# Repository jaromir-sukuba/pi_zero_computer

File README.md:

# Raspberry pi portable computer #

## What it is ##
This is small handheld computer, built around Raspberry Pi Zero, referred as RPi in following articles. Though RPi is often thought to be complete computer, it isn't. You need to add some kind of display, input devices (mouse, keyboard or similar), power supply and perhaps network connection to make it usable by today standards.

My decision was to pack it into small portable form. Raspberry pi laptops have been done to death online, but all of them do miss some features I like to have:

1. All-in-one form factor. I don't want one box for brains, another box for BT keyboard, another for USB hub etc... It is simpler from construction point of view, but the device isn't much usable nor portable.
2. Enclosure sturdy enough so I can put the computer into by backpack with no worries of its disintegration. 
3. At least two USB ports, audio output, battery life at least 5 hours.
4. No major modifications to Raspberry pi. 
5. Easy to replicate by others. I mean - off the shelf components, no complicated wiring (once the PCB is done).

I must admit this computer goes in line with my long term "portable computer fixation", exhibited [before](https://hackaday.io/project/18445-brainfcktor), [and here](https://hackaday.io/project/3511-pavapro-portable-avr-programmer), [also here](https://hackaday.io/project/1757-pp04-camel-computer) or [here too](https://hackaday.io/project/643-minibsd-laptop-computer).

## What it isn't ##
This device isn't superior to thousands or millions manhours of cummulative work put even into the cheapest smartphone you can buy at usual sources. Despite all the work invested into the devices, those are fit to majority of users and (from obvious reasons) often miss details vital for folks like me - full sized USB ports or GPIO pins attached to main processor or 3,5mm audio jack.

## FAQ ##
Q: How is this better than my phone/tablet/smart toaster?

A: If you need to ask this question, then it isn't any better.

## Hardware ##
All hardware is monted on two PCBs, sandwitched together.

The smaller one contains TFT display and a few minor components, vast majority of components is on bottom PCB.

The circuit seems to be complex, but in fact it's only a bit convoluted power supply and user interface. 

RPi acts as heart of this, with USB hub based on FE1.1s, attached to WiFi module, STM32F072 enumerating as USB HID device with two interfaces - one for keyboard (operated by 4x4 matrix keyboard) and one for mouse (operated by analog joystick and three discrete buttons). Audio comes as no surprise to Raspberry pi users, it done by low-pass RC filter and jelly-bean TDA1308 in most common circuit. STM32L011 is connected to RPi by means of serial interface and can turn on/off three power supply voltages (for RPi, for USB, for WiFi) on request of RPi or user. Power is taken from two LiPo cells in series, those are charged by MCP73844 from external 10V source.

Enclosure is designed in FreeCad and printed on hobbyist grade DIY 3D printer

Though self tapered screws would do the job too, I used threaded inserts for machined screws, to allow multiple open-close cycles.

Software
I tried to use as little custom software as possible and rely on existing software drivers. That is behind decision of placing the keyboard behind USB HID wall or using RTL8188EUS module for WiFi. Despite that, device doesn't work as-is with mainstream Raspbian distribution, some customized setup is needed.

* download raspbian, create bootable uSD card and put file ssh.txt into /boot of the uSD card - to allow ssh access to RPi
* connect USB-Ethernet convertor into one USB port of device. 3USD one from Asian sources will do the job
* start device, wait a bit, discover it's IP, login, run raspi-config, setup new password, expand filesystem
* run sudo apt-get update
* run sudo apt-get upgrade
* Add to file /etc/modules-load.d/fbtft.conf
> 	spi-bcm2835
> 	fbtft_device

* Add to file /etc/modprobe.d/fbtft.conf
> 	options fbtft_device custom name=fb_ili9341 gpios=reset:25,dc:24,led:18 speed=16000000 rotate=90 bgr=1

* sudo nano /boot/config.txt
> 	dtoverlay=rpi-display

* sudo reboot
*	sudo nano /boot/cmdline.txt
	
> 	fbcon=map:10 fbcon=font:VGA7x14 logo.nologo

*	sudo nano /usr/share/X11/xorg.conf.d/99-fbdev.conf
> 		Section "Device"
> 		  Identifier "bla"
> 		  Driver "fbdev"
> 		  Option "fbdev" "/dev/fb1"
> 		EndSection
 		
 now you should be able to see display working

* in /boot/config.txt add the following line to enable audio interface:
>     dtoverlay=pwm-2chan,pin=18,func=2,pin2=13,func2=4
>     audio_pwm_mode=2
	
* sudo reboot
* sudo apt-get purge rfkill - to prevent WiFi module from sleeping

## Arduino, just for blog cred ##
Yes, you can upload your arduino sketches in the field

## Miscellany ##
More info is to be found on my [hackady.io page](https://hackaday.io/project/19437-raspberry-pi-zero-handheld-computer)

This project is licensed by MIT license, see LICENSE.md file

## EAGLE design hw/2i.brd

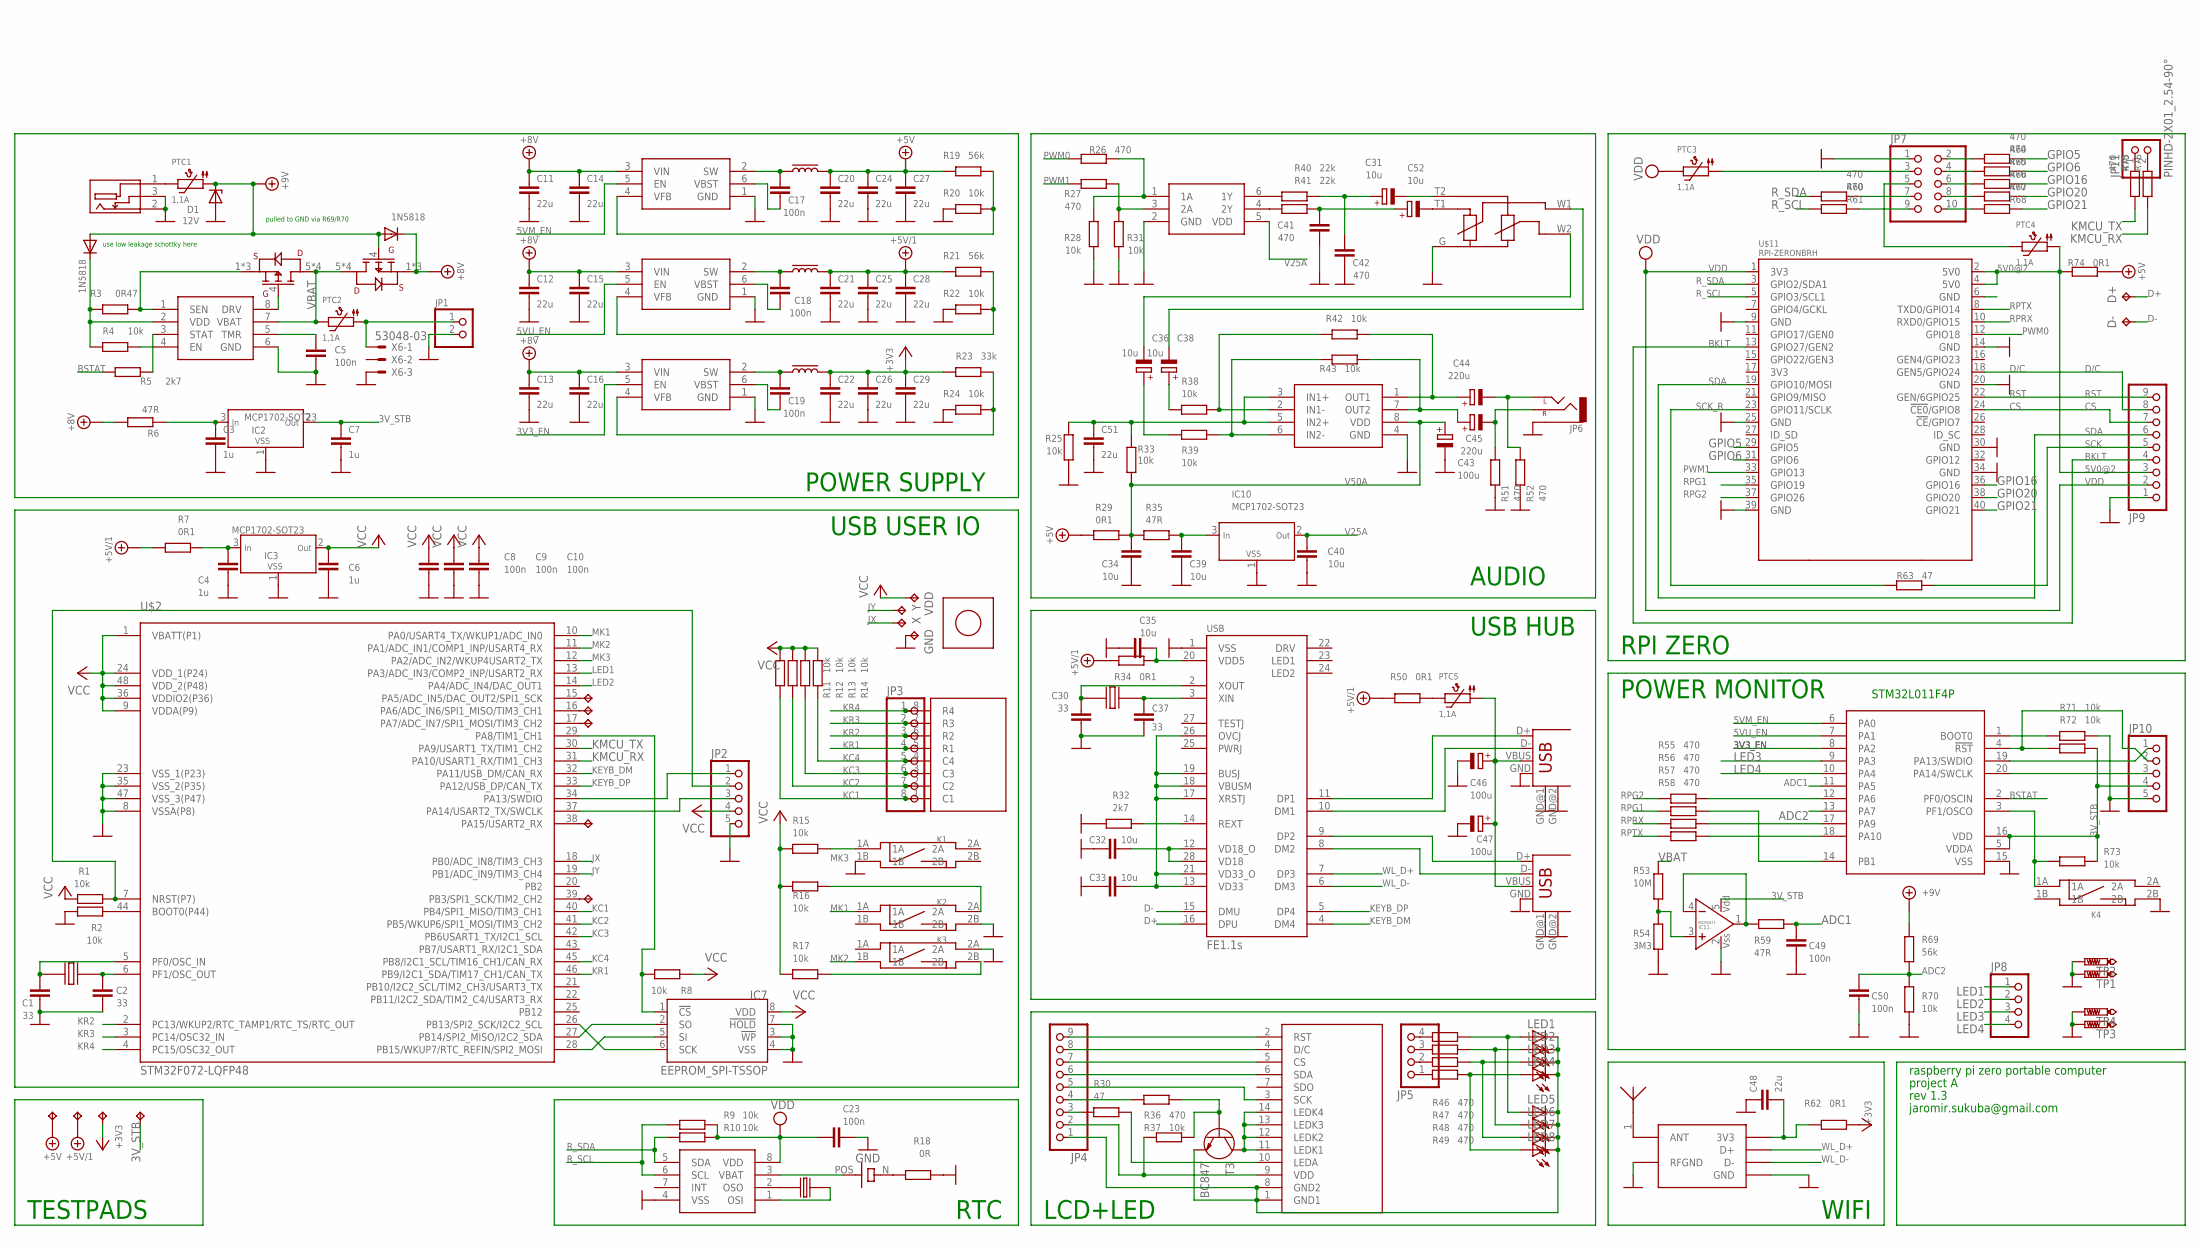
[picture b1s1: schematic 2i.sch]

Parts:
ANT1: ANT_RAINSUN_24GHZ; ANT_RAINSUN-24G
C1, C2, C30, C37: 33; R0805
C3, C4, C6, C7: 1u; R0805
C5, C8, C9, C10, C17, C18, C19, C23, C49, C50: 100n; R0805
C11, C12, C13, C14, C15, C16, C20, C21, C22, C24, C25, C26, C27, C28, C29, C48, C51: 22u; R0805
C31, C36, C38, C52: 10u; PANASONIC_A
C32, C33, C34, C35, C39, C40: 10u; R0805
C41, C42: 470; R0805
C43, C46, C47: 100u; PANASONIC_D
C44, C45: 220u; PANASONIC_D
D1: 12V; SMB
D2, D3: 1N5818; SMB
D+: TPTP14R; TP14R
D-: TPTP14R; TP14R
GND: TPTP14R; TP14R
IC1: MCP73844; MSOP8
IC2, IC3, IC10: MCP1702-SOT23; SOT23
IC4, IC5, IC6: TPS562200; SOT23-6
IC7: EEPROM_SPI-TSSOP; TSSOP8W
IC8: PCF8523; SO-08
IC9: 74LVC2G34; SOT23-6
IC11: MCP6021; SOT23-5L
JP1: PINHD-1X02_2.54-90°; 1X02/90
JP2, JP10: PINHD-1X05_2.54-90°; 1X05/90
JP3: PINHD-1X08_2.54; 1X08
JP4, JP9: PINHD-1X09_2.00; 1X09M
JP5, JP8: PINHD-1X04_2.00; 1X04M
JP6: AUDIO-JACKPTH; AUDIO-JACK
JP7: PINHD-2X05_2.54-90°; 2X05/90
JP11: PINHD-2X01_2.54-90°; 2X01/90
K1, K2, K3, K4: SWITCH_BD_B; SW_SMD2
LED1, LED2, LED3, LED4: LED3MM
LED5, LED6, LED7, LED8: LEDCHIPLED_0805; CHIPLED_0805
MOD1: MOD_USB_RTL8188
PTC1, PTC2, PTC3, PTC4, PTC5: 1,1A; PTC1812
Q1: CRYSTAL87X38; CRYST_32K_87X38MM
R1, R2, R4, R8, R9, R10, R11, R12, R13, R14, R15, R16, R17, R20, R22, R24, R25, R28, R31, R33, R37, R38, R39, R42, R43, R70, R71, R72, R73: 10k; R0805
R3: 0R47; R1206
R5, R32: 2k7; R0805
R6, R35, R59: 47R; R0805
R7, R29, R34, R50, R62, R74: 0R1; R1206
R18: 0R; R0805
R19, R21, R69: 56k; R0805
R23: 33k; R0805
R26, R27, R36, R46, R47, R48, R49, R51, R52, R55, R56, R57, R58, R60, R61, R64, R65, R66, R67, R68, R75, R76: 470; R0805
R30, R63: 47; R0805
R40, R41: 22k; R0805
R53: 10M; R0805
R54: 3M3; R0805
T1, T2: PFET_SO8; SO-08
T3: BC847; SOT23
TFT1: DISP_ILI_28
TP1, TP2, TP3, TP4: PTR1PAD1-13; P1-13
U$1: CONN_DC_13; CON_DC13
U$2: STM32F072-LQFP48; LQFP48
U$3, U$4, U$5: 2u2; BOURNS_SRP7030
U$6: BATTH1220; BATT_HOLDER_DS1092-12
U$7: KB1604
U$8: JOY_PS
U$9: TDA1308; SO-08
U$10: POT_DUAL_14X2; POT_14X2DUAL
U$11: RPI-ZERONBRH; RPI_ZERO_NBRH
U$12: STM32F030_20; TSSOP20
USB: FE1.1S; FE1.1S_SSOP-28
USB1, USB2: USB-A-S
VDD: TPTP14R; TP14R
X, X1, X3, X4, X5, X7, X8, X9, X12, X13: TPTP14R; TP14R
X2, X14: CRYST_TC26SMXAS; CR_12SMXA_S
X6: 53048-03
Y: TPTP14R; TP14R

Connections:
3V3_EN: IC6.5 (EN), U$12.8 (PA2)
3V_STB: C7.1, IC2.2 (OUT), IC11.5 (VDD), JP10.4, R72.2, R73.2, U$12.5 (VDDA), U$12.16 (VDD), X5.TP
5V0@2: JP9.3, PTC4.P$1 (1), R74.2, U$11.2 (5V0), U$11.4 (5V0)
5VM_EN: IC4.5 (EN), U$12.6 (PA0)
5VU_EN: IC5.5 (EN), U$12.7 (PA1)
+3V3: C22.1, C26.1, C29.1, R23.1, R62.1, U$5.P$2, X4.TP
+5V: C20.1, C24.1, C27.1, R19.1, R29.2, R74.1, U$3.P$2, X1.TP
+5V/1: C21.1, C25.1, C28.1, R7.1, R21.1, R34.2, R50.2, U$4.P$2, X3.TP
+8V: C11.1, C12.1, C13.1, C14.1, C15.1, C16.1, D3.C, IC4.3 (VIN), IC5.3 (VIN), IC6.3 (VIN), R6.2, T2.1 (S), T2.2 (S), T2.3 (S)
+9V: D1.C, D2.A, D3.A, PTC1.P$1 (1), R69.2, T2.4 (G)
ADC1: C49.2, R59.1, U$12.11 (PA5)
ADC2: C50.2, R69.1, R70.2, U$12.13 (PA7)
BKLT: JP9.4, U$11.13 (GPIO27/GEN2)
BSTAT: R5.2, U$12.2 (PF0/OSCIN)
CS: JP9.7, U$11.24 (!CE0!/GPIO8)
D+: D+.TP, USB.16 (DPU)
D-: D-.TP, USB.15 (DMU)
D/C: JP9.8, U$11.18 (GEN5/GPIO24)
GND: C1.1, C2.1, C3.2, C4.2, C5.2, C6.2, C7.2, C8.2, C9.2, C10.2, C11.2, C12.2, C13.2, C14.2, C15.2, C16.2, C20.2, C21.2, C22.2, C23.2, C24.2, C25.2, C26.2, C27.2, C28.2, C29.2, C30.1, C32.1, C33.1, C34.1, C35.1, C37.1, C39.1, C40.1, C41.1, C42.1, C43.-, C46.-, C47.-, C48.1, C49.1, C50.1, C51.2, D1.A, GND.TP, IC1.6 (GND), IC2.1 (VSS), IC3.1 (VSS), IC4.1 (GND), IC5.1 (GND), IC6.1 (GND), IC7.3 (!WP), IC7.4 (VSS), IC7.7 (!HOLD), IC8.4 (VSS), IC9.2 (GND), IC10.1 (VSS), IC11.2 (VSS), JP1.2, JP2.5, JP6.SLEEVE, JP7.1, JP9.1, JP10.5, K1.1B, K2.2B, K3.2A, K4.2B, MOD1.GND, MOD1.RFGND, R2.2, R18.1, R20.1, R22.1, R24.1, R25.1, R28.1, R31.1, R32.1, R51.2, R52.2, R54.1, R70.1, R71.2, TP1.TP, TP2.TP, TP3.TP, TP4.TP, U$1.2 (N), U$1.3 (SW), U$2.8 (VSSA(P8)), U$2.23 (VSS_1(P23)), U$2.35 (VSS_2(P35)), U$2.47 (VSS_3(P47)), U$9.4 (GND), U$10.G, U$11.9 (GND), U$11.14 (GND), U$11.20 (GND), U$11.25 (GND), U$11.30 (GND), U$11.34 (GND), U$11.39 (GND), U$12.15 (VSS), USB.1 (VSS), USB1.GND, USB1.GND@1 (GND), USB1.GND@2 (GND), USB2.GND, USB2.GND@1 (GND), USB2.GND@2 (GND), X6.3
GND@8: U$11.6 (GND)
GPIO5: R64.2, U$11.29 (GPIO5)
GPIO6: R65.2, U$11.31 (GPIO6)
GPIO16: R66.2, U$11.36 (GPIO16)
GPIO20: R67.2, U$11.38 (GPIO20)
GPIO21: R68.2, U$11.40 (GPIO21)
JX: U$2.18 (PB0/ADC_IN8/TIM3_CH3), X.TP
JY: U$2.19 (PB1/ADC_IN9/TIM3_CH4), Y.TP
KC1: JP3.8, R11.1, U$2.40 (PB4/SPI1_MISO/TIM3_CH1), U$7.1 (C1)
KC2: JP3.7, R12.1, U$2.41 (PB5/WKUP6/SPI1_MOSI/TIM3_CH2), U$7.2 (C2)
KC3: JP3.6, R13.1, U$2.42 (PB6USART1_TX/I2C1_SCL), U$7.3 (C3)
KC4: JP3.5, R14.1, U$2.45 (PB8/I2C1_SCL/TIM16_CH1/CAN_RX), U$7.4 (C4)
KEYB_DM: U$2.32 (PA11/USB_DM/CAN_RX), USB.4 (DM4)
KEYB_DP: U$2.33 (PA12/USB_DP/CAN_TX), USB.5 (DP4)
KMCU_RX: R76.1, U$2.31 (PA10/USART1_RX/TIM1_CH3)
KMCU_TX: R75.1, U$2.30 (PA9/USART1_TX/TIM1_CH2)
KR1: JP3.4, U$2.46 (PB9/I2C1_SDA/TIM17_CH1/CAN_TX), U$7.5 (R1)
KR2: JP3.3, U$2.2 (PC13/WKUP2/RTC_TAMP1/RTC_TS/RTC_OUT), U$7.6 (R2)
KR3: JP3.2, U$2.3 (PC14/OSC32_IN), U$7.7 (R3)
KR4: JP3.1, U$2.4 (PC15/OSC32_OUT), U$7.8 (R4)
LED1: JP8.1, U$2.13 (PA3/ADC_IN3/COMP2_INP/USART2_RX)
LED2: JP8.2, U$2.14 (PA4/ADC_IN4/DAC_OUT1)
LED3: JP8.3, U$12.9 (PA3)
LED4: JP8.4, U$12.10 (PA4)
MK1: K2.1A, U$2.10 (PA0/USART4_TX/WKUP1/ADC_IN0)
MK2: K3.1B, U$2.11 (PA1/ADC_IN1/COMP1_INP/USART4_RX)
MK3: K1.1A, R15.2, U$2.12 (PA2/ADC_IN2/WKUP4USART2_TX)
unnamed: C35.2, R34.1, USB.20 (VDD5)
unnamed: C17.2, IC4.2 (SW), U$3.P$1
unnamed: JP4.3, R30.2
unnamed: IC7.6 (SCK), U$2.26 (PB13/SPI2_SCK/I2C2_SCL)
unnamed: R36.2, R37.1, T3.1 (B)
unnamed: JP4.4, R36.1
unnamed: IC1.1 (SEN), R3.2, T1.1 (S), T1.2 (S), T1.3 (S)
unnamed: USB.9 (DP2), USB2.D+
unnamed: USB.8 (DM2), USB2.D-
unnamed: USB.10 (DM1), USB1.D-
unnamed: IC1.8 (DRV), T1.4 (G)
unnamed: IC1.4 (EN), R4.2
unnamed: USB.11 (DP1), USB1.D+
unnamed: C33.2, USB.13 (VD33), USB.17 (XRSTJ), USB.18 (VBUSM), USB.19 (BUSJ), USB.21 (VD33_O), USB.26 (OVCJ)
unnamed: IC11.1 (VYSTUP), IC11.4 (IN-), R59.2
unnamed: C32.2, USB.12 (VD18_O), USB.28 (VD18)
unnamed: C5.1, IC1.5 (TMR)
unnamed: C17.1, IC4.6 (VBST)
unnamed: R32.2, USB.14 (REXT)
unnamed: IC4.4 (VFB), R19.2, R20.2
unnamed: C30.2, USB.2 (XOUT), X14.P$1
unnamed: C18.2, IC5.2 (SW), U$4.P$1
unnamed: C18.1, IC5.6 (VBST)
unnamed: C37.2, USB.3 (XIN), X14.P$2
unnamed: C46.+, C47.+, PTC5.P$1 (1), USB1.VBUS, USB2.VBUS
unnamed: IC7.2 (SO), U$2.27 (PB14/SPI2_MISO/I2C2_SDA)
unnamed: IC9.6 (1Y), R40.2
unnamed: IC9.4 (2Y), R41.2
unnamed: C31.+, C42.2, R40.1
unnamed: C41.2, C52.+, R41.1
unnamed: C44.-, JP6.TIP (LEFT), R52.1
unnamed: C45.-, JP6.RING (RIGHT), R51.1
unnamed: C44.+, R42.2, U$9.1 (OUT1)
unnamed: C45.+, R43.2, U$9.7 (OUT2)
unnamed: C51.1, R25.2, R33.1, U$9.3 (IN1+), U$9.5 (IN2+)
unnamed: R38.2, R42.1, U$9.2 (IN1-)
unnamed: R39.2, R43.1, U$9.6 (IN2-)
unnamed: C38.+, R38.1
unnamed: C36.+, R39.1
unnamed: C36.-, U$10.W2
unnamed: C38.-, U$10.W1
unnamed: ANT1.1, MOD1.ANT
unnamed: JP11.1, R75.2
unnamed: IC5.4 (VFB), R21.2, R22.2
unnamed: C19.2, IC6.2 (SW), U$5.P$1
unnamed: C19.1, IC6.6 (VBST)
unnamed: JP2.1, U$2.34 (PA13/SWDIO)
unnamed: IC6.4 (VFB), R23.2, R24.2
unnamed: C4.1, IC3.3 (IN), R7.2
unnamed: JP2.3, U$2.37 (PA14/USART2_TX/SWCLK)
unnamed: D2.C, IC1.2 (VDD), R3.1, R4.1
unnamed: PTC1.P$2 (2), U$1.1
unnamed: IC9.1 (1A), R26.1, R28.2
unnamed: IC9.3 (2A), R27.1, R31.2
unnamed: C1.2, U$2.5 (PF0/OSC_IN), X2.P$1
unnamed: JP11.2, R76.2
unnamed: IC7.5 (SI), U$2.28 (PB15/WKUP7/RTC_REFIN/SPI2_MOSI)
unnamed: IC7.1 (!CS), R8.2, U$2.29 (PA8/TIM1_CH1)
unnamed: R56.2, U$12.14 (PB1)
unnamed: U$2.15 (PA5/ADC_IN5/DAC_OUT2/SPI1_SCK), X7.TP
unnamed: R2.1, U$2.44 (BOOT0(P44))
unnamed: JP5.4, R46.2
unnamed: JP5.3, R47.2
unnamed: JP5.2, R48.2
unnamed: JP5.1, R49.2
unnamed: JP2.2, R1.1, U$2.7 (NRST(P7))
unnamed: R57.2, U$12.17 (PA9)
unnamed: R58.2, U$12.18 (PA10)
unnamed: PTC5.P$2 (2), R50.1
unnamed: R55.2, U$12.12 (PA6)
unnamed: U$2.16 (PA6/ADC_IN6/SPI1_MISO/TIM3_CH1), X8.TP
unnamed: U$2.17 (PA7/ADC_IN7/SPI1_MOSI/TIM3_CH2), X9.TP
unnamed: U$2.38 (PA15/USART2_RX), X12.TP
unnamed: U$2.39 (PB3/SPI1_SCK/TIM2_CH2), X13.TP
unnamed: JP10.1, U$12.19 (PA13/SWDIO)
unnamed: JP10.3, U$12.20 (PA14/SWCLK)
unnamed: JP10.2, R72.1, U$12.4 (!RST)
unnamed: JP1.1, PTC2.P$1 (1), X6.1
unnamed: C52.-, U$10.T1
unnamed: K4.1A, R73.1, U$12.3 (PF1/OSCO)
unnamed: C2.2, U$2.6 (PF1/OSC_OUT), X2.P$2
unnamed: IC8.3 (VBAT), U$6.POS
unnamed: R18.2, U$6.N (M)
unnamed: LED1.A, LED5.A, R46.1
unnamed: LED2.A, LED6.A, R47.1
unnamed: K3.2B, R17.2
unnamed: IC8.2 (OSO), Q1.4 (2)
unnamed: IC8.1 (OSI), Q1.1
unnamed: K2.2A, R16.2
unnamed: LED3.A, LED7.A, R48.1
unnamed: LED4.A, LED8.A, R49.1
unnamed: JP4.5, TFT1.3 (SCK)
unnamed: JP4.1, LED1.K (C), LED2.K (C), LED3.K (C), LED4.K (C), LED5.C, LED6.C, LED7.C, LED8.C, T3.2 (E), TFT1.1 (GND1), TFT1.8 (GND2)
unnamed: T3.3 (C), TFT1.11 (LEDK1), TFT1.12 (LEDK2), TFT1.13 (LEDK3), TFT1.14 (LEDK4)
unnamed: JP7.5, PTC4.P$2 (2)
unnamed: IC1.3 (STAT), R5.1
unnamed: JP7.3, PTC3.P$1 (1)
unnamed: C48.2, MOD1.3V3, R62.2
unnamed: IC11.3 (NEIN+), R53.1, R54.2
unnamed: C3.1, IC2.3 (IN), R6.1
unnamed: R71.1, U$12.1 (BOOT0)
unnamed: C31.-, U$10.T2
unnamed: R30.1, TFT1.10 (LEDA)
unnamed: JP4.2, R37.2, TFT1.9 (VDD)
unnamed: C39.2, IC10.3 (IN), R35.2
unnamed: JP4.6, TFT1.6 (SDA)
unnamed: JP4.7, TFT1.5 (CS)
unnamed: JP4.8, TFT1.4 (D/C)
unnamed: JP4.9, TFT1.2 (RST)
unnamed: JP7.10, R68.1
unnamed: JP7.8, R67.1
unnamed: JP7.6, R66.1
unnamed: JP7.4, R65.1
unnamed: JP7.2, R64.1
unnamed: JP7.7, R60.2
unnamed: JP7.9, R61.2
PWM0: R27.2, U$11.12 (GPIO18)
PWM1: R26.2, U$11.33 (GPIO13)
RPG1: R56.1, U$11.35 (GPIO19)
RPG2: R55.1, U$11.37 (GPIO26)
RPRX: R57.1, U$11.10 (RXD0/GPIO15)
RPTX: R58.1, U$11.8 (TXD0/GPIO14)
RST: JP9.9, U$11.22 (GEN/6GPIO25)
R_SCL: IC8.6 (SCL), R9.1, R61.1, U$11.5 (GPIO3/SCL1)
R_SDA: IC8.5 (SDA), R10.1, R60.1, U$11.3 (GPIO2/SDA1)
SCK: JP9.5, R63.1
SCK_R: R63.2, U$11.23 (GPIO11/SCLK)
SDA: JP9.6, U$11.19 (GPIO10/MOSI)
V25A: C40.2, IC9.5 (VDD), IC10.2 (OUT)
V50A: C34.2, C43.+, R29.1, R33.2, R35.1, U$9.8 (VDD)
VBAT: IC1.7 (VBAT), PTC2.P$2 (2), R53.2, T1.5 (D), T1.6 (D), T1.7 (D), T1.8 (D), T2.5 (D), T2.6 (D), T2.7 (D), T2.8 (D)
VCC: C6.1, C8.1, C9.1, C10.1, IC3.2 (OUT), IC7.8 (VDD), JP2.4, R1.2, R8.1, R11.2, R12.2, R13.2, R14.2, R15.1, R16.1, R17.1, U$2.1 (VBATT(P1)), U$2.9 (VDDA(P9)), U$2.24 (VDD_1(P24)), U$2.36 (VDDIO2(P36)), U$2.48 (VDD_2(P48)), VDD.TP
VDD: C23.1, IC8.8 (VDD), JP9.2, PTC3.P$2 (2), R9.2, R10.2, U$11.1 (3V3)
WL_D+: MOD1.D+, USB.7 (DP3)
WL_D-: MOD1.D-, USB.6 (DM3)

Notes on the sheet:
POWER SUPPLY
USB USER IO
RPI ZERO
POWER MONITOR
WIFI
LCD+LED
USB HUB
AUDIO
raspberry pi zero portable computer
project A
rev 1.3
RTC
jaromir.sukuba@gmail.com
pulled to GND via R69/R70
use low leakage schottky here
TESTPADS
STM32L011F4P

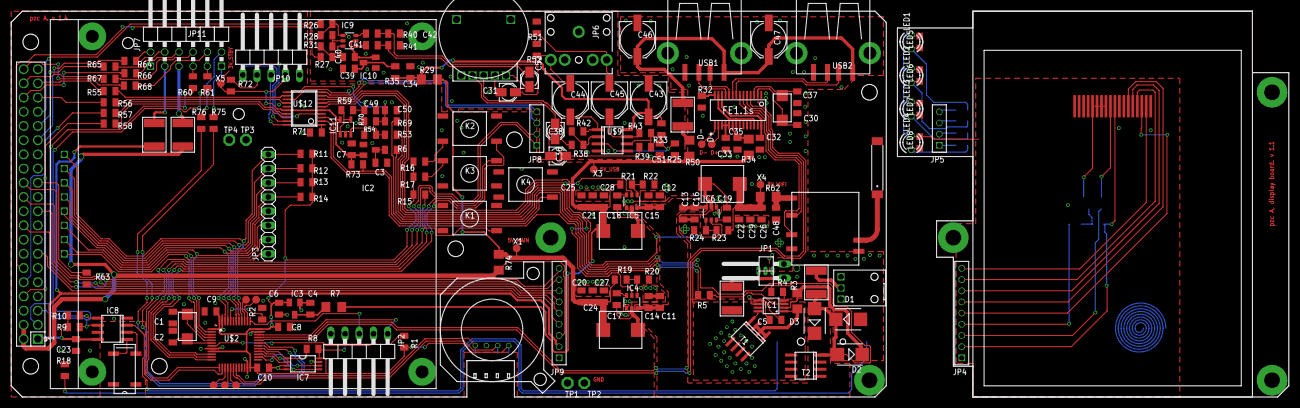
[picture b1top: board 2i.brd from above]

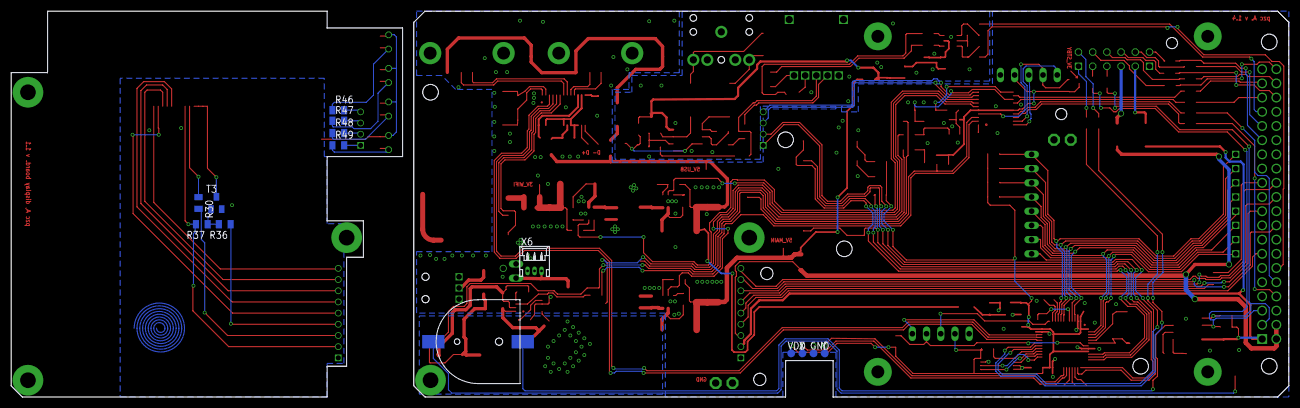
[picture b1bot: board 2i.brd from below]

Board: 2 copper layers, 228.5 x 69.0 mm, 212 parts (14 on the bottom side), 180 nets.

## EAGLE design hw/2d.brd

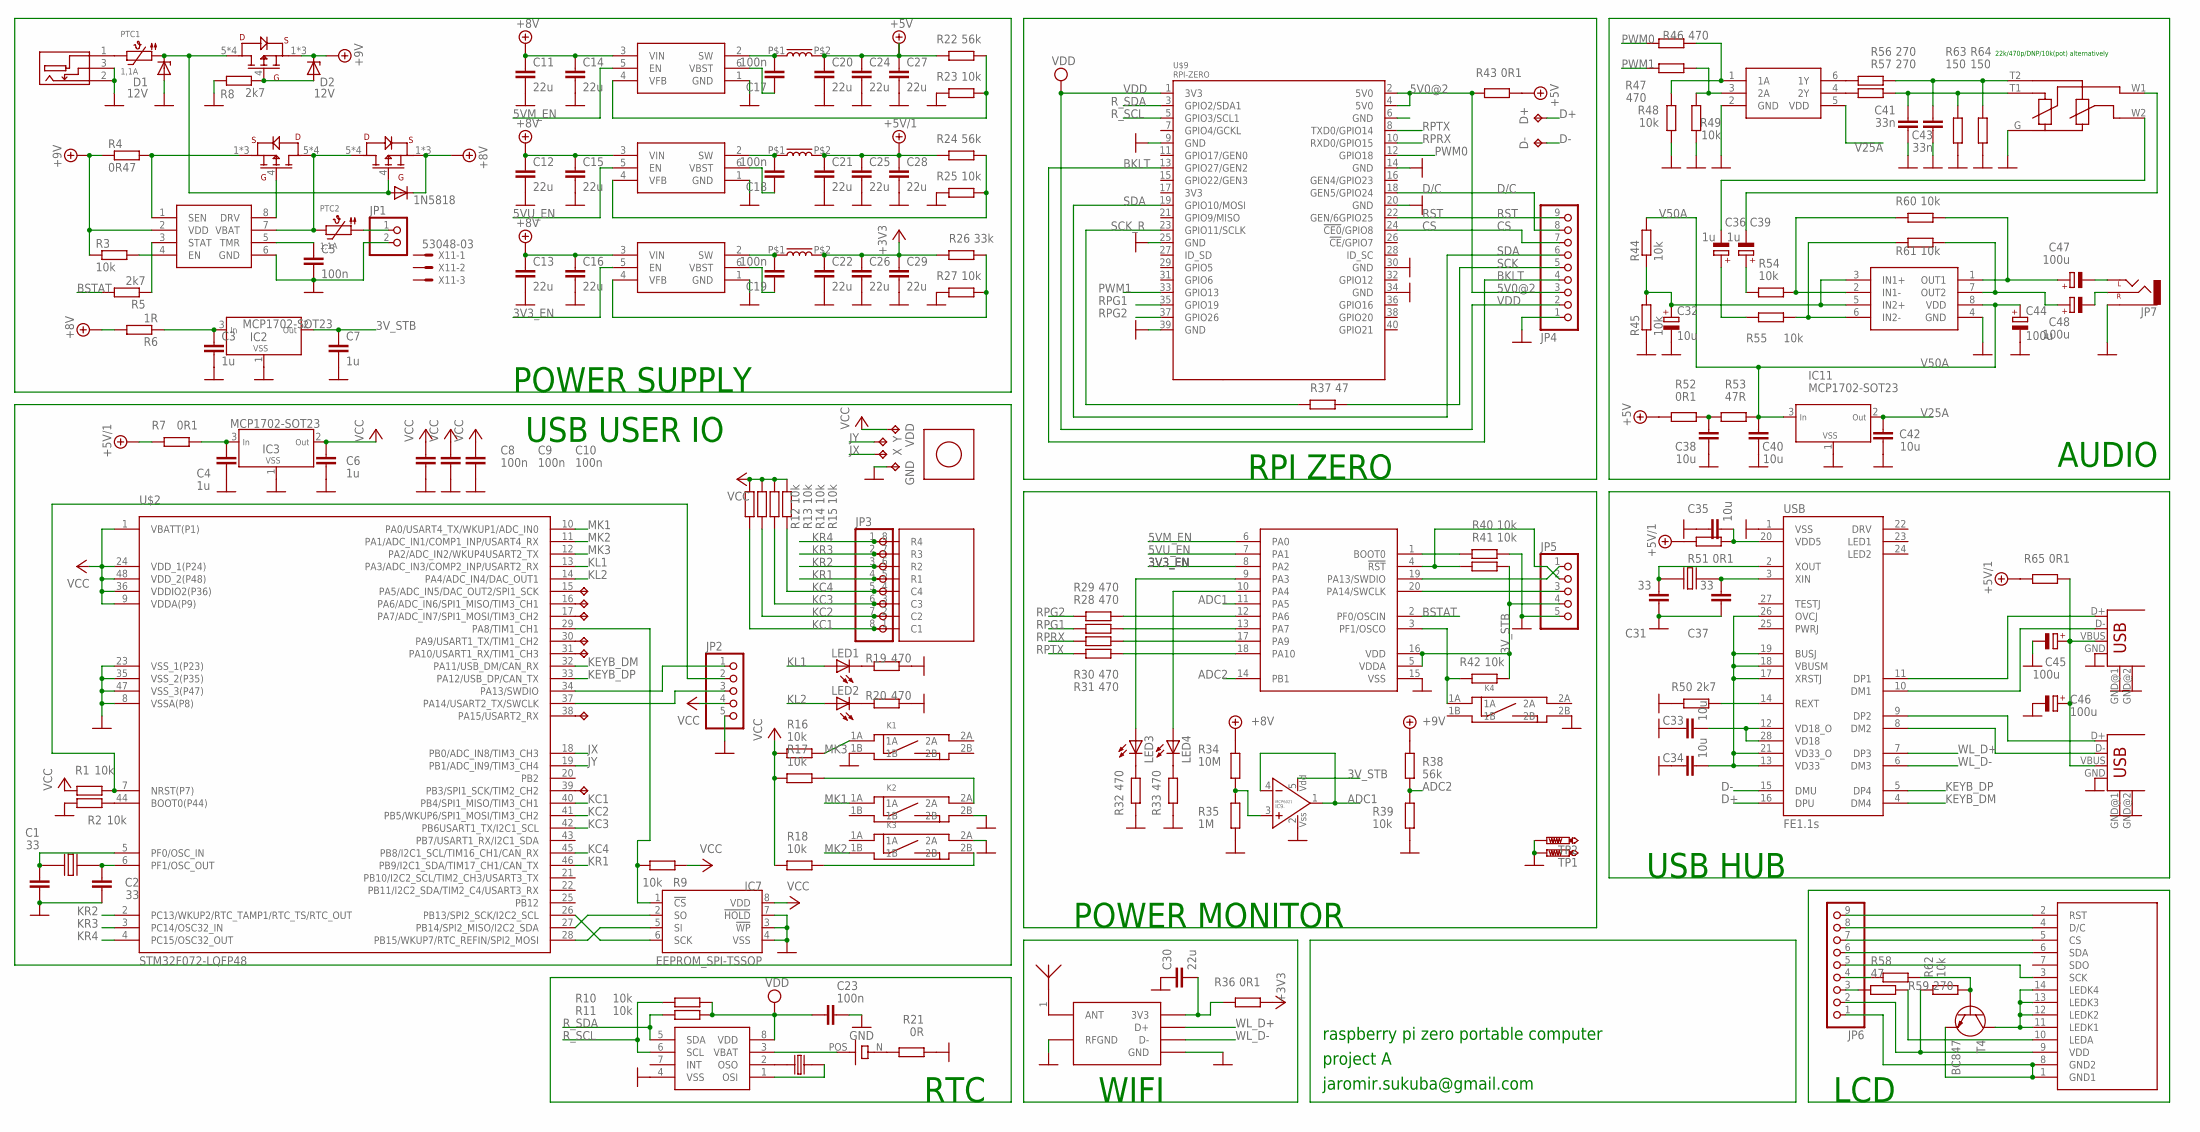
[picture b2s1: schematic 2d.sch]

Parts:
ANT1: ANT_RAINSUN_24GHZ; ANT_RAINSUN-24G
C1, C2, C31, C37: 33; R0805
C3, C4, C6, C7: 1u; R0805
C5, C8, C9, C10, C17, C18, C19, C23: 100n; R0805
C11, C12, C13, C14, C15, C16, C20, C21, C22, C24, C25, C26, C27, C28, C29, C30: 22u; R0805
C32: 10u; PANASONIC_B
C33, C34, C35, C38, C40, C42: 10u; R0805
C36, C39: 1u; PANASONIC_A
C41, C43: 33n; R0805
C44, C45, C46, C47, C48: 100u; PANASONIC_D
D1: 12V; SMB
D2: 12V; SOD80C
D3: 1N5818; SMB
D+: TPTP14R; TP14R
D-: TPTP14R; TP14R
GND: TPTP14R; TP14R
IC1: MCP73844; MSOP8
IC2, IC3, IC11: MCP1702-SOT23; SOT23
IC4, IC5, IC6: TPS562200; SOT23-6
IC7: EEPROM_SPI-TSSOP; TSSOP8W
IC8: PCF8523; SO-08
IC9: MCP6021; SOT23-5L
IC10: 74LVC2G34; SOT23-6
JP1: PINHD-1X02_2.54-90°; 1X02/90
JP2, JP5: PINHD-1X05_2.54-90°; 1X05/90
JP3: PINHD-1X08_2.54; 1X08
JP4, JP6: PINHD-1X09_2.00; 1X09M
JP7: AUDIO-JACKPTH; AUDIO-JACK
K1, K2, K3, K4: SWITCH_BD_B; SW_SMD2
LED1, LED2, LED3, LED4: LED3MM
MOD1: MOD_USB_RTL8188
PTC1, PTC2: 1,1A; PTC1812
Q1: CRYSTAL87X38; CRYST_32K_87X38MM
R1, R2, R3, R9, R10, R11, R12, R13, R14, R15, R16, R17, R18, R23, R25, R27, R39, R40, R41, R42, R44, R45, R48, R49, R54, R55, R60, R61, R62: 10k; R0805
R4: 0R47; R1206
R5, R8, R50: 2k7; R0805
R6: 1R; R0805
R7, R36, R43, R51, R52, R65: 0R1; R1206
R19, R20, R28, R29, R30, R31, R32, R33, R46, R47: 470; R0805
R21: 0R; R0805
R22, R24, R38: 56k; R0805
R26: 33k; R0805
R34: 10M; R0805
R35: 1M; R0805
R37, R58: 47; R0805
R53: 47R; R0805
R56, R57, R59: 270; R0805
R63, R64: 150; R0805
T1, T2, T3: PFET_SO8; SO-08
T4: BC847; SOT23
TFT1: DISP_ILI_28
TP1, TP2: PTR1PAD1-13; P1-13
U$1: CONN_DC_13; CON_DC13
U$2: STM32F072-LQFP48; LQFP48
U$3, U$4, U$5: 2u2; BOURNS_SRP7030
U$6: BATTH1220; BATT_HOLDER_DS1092-12
U$7: KB1604
U$8: JOY_PS
U$9: RPI-ZERO; RASPBERRYPI_BASTELSTUBE_V13_RASPI_BOARD_B+_FULL
U$10: STM32F030_20; TSSOP20
U$11: TDA1308; SO-08
U$12: POT_DUAL_14X2; POT_14X2DUAL
USB: FE1.1S; FE1.1S_SSOP-28
USB1, USB2: USB-A-S
VDD: TPTP14R; TP14R
X, X2, X3, X4, X5, X6, X7, X8: TPTP14R; TP14R
X1, X9: CRYST_TC26SMXAS; CR_12SMXA_S
X11: 53048-03
Y: TPTP14R; TP14R

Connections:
3V3_EN: IC6.5 (EN), U$10.8 (PA2)
3V_STB: C7.1, IC2.2 (OUT), IC9.5 (VDD), JP5.4, R41.2, R42.2, U$10.5 (VDDA), U$10.16 (VDD)
5V0@2: JP4.3, R43.2, U$9.2 (5V0), U$9.4 (5V0)
5VM_EN: IC4.5 (EN), U$10.6 (PA0)
5VU_EN: IC5.5 (EN), U$10.7 (PA1)
+3V3: C22.1, C26.1, C29.1, R26.1, R36.1, U$5.P$2
+5V: C20.1, C24.1, C27.1, R22.1, R43.1, R52.2, U$3.P$2
+5V/1: C21.1, C25.1, C28.1, R7.1, R24.1, R51.2, R65.2, U$4.P$2
+8V: C11.1, C12.1, C13.1, C14.1, C15.1, C16.1, D3.C, IC4.3 (VIN), IC5.3 (VIN), IC6.3 (VIN), R6.2, R34.2, T3.1 (S), T3.2 (S), T3.3 (S)
+12V: D2.C, IC1.2 (VDD), R3.1, R4.1, R38.2, T1.1 (S), T1.2 (S), T1.3 (S)
ADC1: IC9.1 (VYSTUP), IC9.4 (IN-), U$10.11 (PA5)
ADC2: R38.1, R39.2, U$10.14 (PB1)
BKLT: JP4.4, U$9.13 (GPIO27/GEN2)
BSTAT: R5.2, U$10.2 (PF0/OSCIN)
CS: JP4.7, U$9.24 (!CE0!/GPIO8)
D+: D+.TP, USB.16 (DPU)
D-: D-.TP, USB.15 (DMU)
D/C: JP4.8, U$9.18 (GEN5/GPIO24)
GND: C1.1, C2.1, C3.2, C4.2, C5.2, C6.2, C7.2, C8.2, C9.2, C10.2, C11.2, C12.2, C13.2, C14.2, C15.2, C16.2, C20.2, C21.2, C22.2, C23.2, C24.2, C25.2, C26.2, C27.2, C28.2, C29.2, C30.1, C31.1, C32.-, C33.1, C34.1, C35.1, C37.1, C38.1, C40.1, C41.1, C42.1, C43.1, C44.-, C45.-, C46.-, D1.A, GND.TP, IC1.6 (GND), IC2.1 (VSS), IC3.1 (VSS), IC4.1 (GND), IC5.1 (GND), IC6.1 (GND), IC7.3 (!WP), IC7.4 (VSS), IC7.7 (!HOLD), IC8.4 (VSS), IC9.2 (VSS), IC10.2 (GND), IC11.1 (VSS), JP1.2, JP2.5, JP4.1, JP5.5, JP7.SLEEVE, K1.1B, K2.2B, K3.2A, K4.2B, MOD1.GND, MOD1.RFGND, R2.2, R8.1, R19.1, R20.1, R21.1, R23.1, R25.1, R27.1, R32.1, R33.1, R35.1, R39.1, R40.2, R45.1, R48.1, R49.1, R50.1, R63.2, R64.2, TP1.TP, TP2.TP, U$1.2 (N), U$1.3 (SW), U$2.8 (VSSA(P8)), U$2.23 (VSS_1(P23)), U$2.35 (VSS_2(P35)), U$2.47 (VSS_3(P47)), U$9.9 (GND), U$9.14 (GND), U$9.20 (GND), U$9.25 (GND), U$9.30 (GND), U$9.34 (GND), U$9.39 (GND), U$10.15 (VSS), U$11.4 (GND), U$12.G, USB.1 (VSS), USB1.GND, USB1.GND@1 (GND), USB1.GND@2 (GND), USB2.GND, USB2.GND@1 (GND), USB2.GND@2 (GND)
GND@8: U$9.6 (GND)
JX: U$2.18 (PB0/ADC_IN8/TIM3_CH3), X.TP
JY: U$2.19 (PB1/ADC_IN9/TIM3_CH4), Y.TP
KC1: JP3.8, R12.1, U$2.40 (PB4/SPI1_MISO/TIM3_CH1), U$7.1 (C1)
KC2: JP3.7, R13.1, U$2.41 (PB5/WKUP6/SPI1_MOSI/TIM3_CH2), U$7.2 (C2)
KC3: JP3.6, R14.1, U$2.42 (PB6USART1_TX/I2C1_SCL), U$7.3 (C3)
KC4: JP3.5, R15.1, U$2.45 (PB8/I2C1_SCL/TIM16_CH1/CAN_RX), U$7.4 (C4)
KEYB_DM: U$2.32 (PA11/USB_DM/CAN_RX), USB.4 (DM4)
KEYB_DP: U$2.33 (PA12/USB_DP/CAN_TX), USB.5 (DP4)
KL1: LED1.A, U$2.13 (PA3/ADC_IN3/COMP2_INP/USART2_RX)
KL2: LED2.A, U$2.14 (PA4/ADC_IN4/DAC_OUT1)
KR1: JP3.4, U$2.46 (PB9/I2C1_SDA/TIM17_CH1/CAN_TX), U$7.5 (R1)
KR2: JP3.3, U$2.2 (PC13/WKUP2/RTC_TAMP1/RTC_TS/RTC_OUT), U$7.6 (R2)
KR3: JP3.2, U$2.3 (PC14/OSC32_IN), U$7.7 (R3)
KR4: JP3.1, U$2.4 (PC15/OSC32_OUT), U$7.8 (R4)
MK1: K2.1A, U$2.10 (PA0/USART4_TX/WKUP1/ADC_IN0)
MK2: K3.1B, U$2.11 (PA1/ADC_IN1/COMP1_INP/USART4_RX)
MK3: K1.1A, R16.2, U$2.12 (PA2/ADC_IN2/WKUP4USART2_TX)
unnamed: C35.2, R51.1, USB.20 (VDD5)
unnamed: C17.2, IC4.2 (SW), U$3.P$1
unnamed: JP6.3, R58.2
unnamed: IC7.6 (SCK), U$2.26 (PB13/SPI2_SCK/I2C2_SCL)
unnamed: R59.2, R62.1, T4.1 (B)
unnamed: JP6.4, R59.1
unnamed: IC1.1 (SEN), R4.2, T2.1 (S), T2.2 (S), T2.3 (S)
unnamed: USB.9 (DP2), USB2.D+
unnamed: USB.8 (DM2), USB2.D-
unnamed: USB.10 (DM1), USB1.D-
unnamed: IC1.8 (DRV), T2.4 (G)
unnamed: IC1.4 (EN), R3.2
unnamed: USB.11 (DP1), USB1.D+
unnamed: C34.2, USB.13 (VD33), USB.17 (XRSTJ), USB.18 (VBUSM), USB.19 (BUSJ), USB.21 (VD33_O), USB.26 (OVCJ)
unnamed: IC1.7 (VBAT), PTC2.P$2 (2), T2.5 (D), T2.6 (D), T2.7 (D), T2.8 (D), T3.5 (D), T3.6 (D), T3.7 (D), T3.8 (D)
unnamed: C33.2, USB.12 (VD18_O), USB.28 (VD18)
unnamed: C5.1, IC1.5 (TMR)
unnamed: C17.1, IC4.6 (VBST)
unnamed: R50.2, USB.14 (REXT)
unnamed: IC4.4 (VFB), R22.2, R23.2
unnamed: C31.2, USB.2 (XOUT), X9.P$1
unnamed: C18.2, IC5.2 (SW), U$4.P$1
unnamed: C18.1, IC5.6 (VBST)
unnamed: C37.2, USB.3 (XIN), X9.P$2
unnamed: C45.+, C46.+, R65.1, USB1.VBUS, USB2.VBUS
unnamed: IC7.2 (SO), U$2.27 (PB14/SPI2_MISO/I2C2_SDA)
unnamed: IC10.6 (1Y), R56.2
unnamed: IC10.4 (2Y), R57.2
unnamed: C43.2, R56.1, R64.1, U$12.T2
unnamed: C41.2, R57.1, R63.1, U$12.T1
unnamed: C47.-, JP7.TIP (LEFT)
unnamed: C48.-, JP7.RING (RIGHT)
unnamed: C47.+, R60.2, U$11.1 (OUT1)
unnamed: C48.+, R61.2, U$11.7 (OUT2)
unnamed: C32.+, R44.1, R45.2, U$11.3 (IN1+), U$11.5 (IN2+)
unnamed: R54.2, R60.1, U$11.2 (IN1-)
unnamed: R55.2, R61.1, U$11.6 (IN2-)
unnamed: C39.+, R54.1
unnamed: C36.+, R55.1
unnamed: C36.-, U$12.W2
unnamed: C39.-, U$12.W1
unnamed: ANT1.1, MOD1.ANT
unnamed: C38.2, R52.1, R53.1
unnamed: IC5.4 (VFB), R24.2, R25.2
unnamed: C19.2, IC6.2 (SW), U$5.P$1
unnamed: C19.1, IC6.6 (VBST)
unnamed: JP2.1, U$2.34 (PA13/SWDIO)
unnamed: IC6.4 (VFB), R26.2, R27.2
unnamed: C4.1, IC3.3 (IN), R7.2
unnamed: JP2.3, U$2.37 (PA14/USART2_TX/SWCLK)
unnamed: D2.A, R8.2, T1.4 (G)
unnamed: PTC1.P$2 (2), U$1.1
unnamed: IC10.1 (1A), R46.1, R48.2
unnamed: IC10.3 (2A), R47.1, R49.2
unnamed: C1.2, U$2.5 (PF0/OSC_IN), X1.P$1
unnamed: U$2.30 (PA9/USART1_TX/TIM1_CH2), X5.TP
unnamed: IC7.5 (SI), U$2.28 (PB15/WKUP7/RTC_REFIN/SPI2_MOSI)
unnamed: IC7.1 (!CS), R9.2, U$2.29 (PA8/TIM1_CH1)
unnamed: U$2.31 (PA10/USART1_RX/TIM1_CH3), X6.TP
unnamed: U$2.15 (PA5/ADC_IN5/DAC_OUT2/SPI1_SCK), X2.TP
unnamed: R2.1, U$2.44 (BOOT0(P44))
unnamed: LED1.K (C), R19.2
unnamed: LED2.K (C), R20.2
unnamed: LED4.A, U$10.10 (PA4)
unnamed: LED3.A, U$10.9 (PA3)
unnamed: JP2.2, R1.1, U$2.7 (NRST(P7))
unnamed: R30.2, U$10.17 (PA9)
unnamed: R31.2, U$10.18 (PA10)
unnamed: R28.2, U$10.13 (PA7)
unnamed: R29.2, U$10.12 (PA6)
unnamed: U$2.16 (PA6/ADC_IN6/SPI1_MISO/TIM3_CH1), X3.TP
unnamed: U$2.17 (PA7/ADC_IN7/SPI1_MOSI/TIM3_CH2), X4.TP
unnamed: U$2.38 (PA15/USART2_RX), X7.TP
unnamed: U$2.39 (PB3/SPI1_SCK/TIM2_CH2), X8.TP
unnamed: JP5.1, U$10.19 (PA13/SWDIO)
unnamed: JP5.3, U$10.20 (PA14/SWCLK)
unnamed: JP5.2, R41.1, U$10.4 (!RST)
unnamed: JP1.1, PTC2.P$1 (1)
unnamed: K4.1A, R42.1, U$10.3 (PF1/OSCO)
unnamed: C2.2, U$2.6 (PF1/OSC_OUT), X1.P$2
unnamed: IC8.3 (VBAT), U$6.POS
unnamed: R21.2, U$6.N (M)
unnamed: LED3.K (C), R32.2
unnamed: LED4.K (C), R33.2
unnamed: K3.2B, R18.2
unnamed: IC8.2 (OSO), Q1.4 (2)
unnamed: IC8.1 (OSI), Q1.1
unnamed: K2.2A, R17.2
unnamed: JP6.5, TFT1.3 (SCK)
unnamed: T4.3 (C), TFT1.11 (LEDK1), TFT1.12 (LEDK2), TFT1.13 (LEDK3), TFT1.14 (LEDK4)
unnamed: IC1.3 (STAT), R5.1
unnamed: C30.2, MOD1.3V3, R36.2
unnamed: IC9.3 (NEIN+), R34.1, R35.2
unnamed: C3.1, IC2.3 (IN), R6.1
unnamed: R40.1, U$10.1 (BOOT0)
unnamed: D1.C, D3.A, PTC1.P$1 (1), T1.5 (D), T1.6 (D), T1.7 (D), T1.8 (D), T3.4 (G)
unnamed: R58.1, TFT1.10 (LEDA)
unnamed: JP6.2, R62.2, TFT1.9 (VDD)
unnamed: JP6.1, T4.2 (E), TFT1.1 (GND1), TFT1.8 (GND2)
unnamed: JP6.6, TFT1.6 (SDA)
unnamed: JP6.7, TFT1.5 (CS)
unnamed: JP6.8, TFT1.4 (D/C)
unnamed: JP6.9, TFT1.2 (RST)
PWM0: R47.2, U$9.12 (GPIO18)
PWM1: R46.2, U$9.33 (GPIO13)
RPG1: R28.1, U$9.35 (GPIO19)
RPG2: R29.1, U$9.37 (GPIO26)
RPRX: R30.1, U$9.10 (RXD0/GPIO15)
RPTX: R31.1, U$9.8 (TXD0/GPIO14)
RST: JP4.9, U$9.22 (GEN/6GPIO25)
R_SCL: IC8.6 (SCL), R10.1, U$9.5 (GPIO3/SCL1)
R_SDA: IC8.5 (SDA), R11.1, U$9.3 (GPIO2/SDA1)
SCK: JP4.5, R37.1
SCK_R: R37.2, U$9.23 (GPIO11/SCLK)
SDA: JP4.6, U$9.19 (GPIO10/MOSI)
V25A: C42.2, IC10.5 (VDD), IC11.2 (OUT)
V50A: C40.2, C44.+, IC11.3 (IN), R44.2, R53.2, U$11.8 (VDD)
VCC: C6.1, C8.1, C9.1, C10.1, IC3.2 (OUT), IC7.8 (VDD), JP2.4, R1.2, R9.1, R12.2, R13.2, R14.2, R15.2, R16.1, R17.1, R18.1, U$2.1 (VBATT(P1)), U$2.9 (VDDA(P9)), U$2.24 (VDD_1(P24)), U$2.36 (VDDIO2(P36)), U$2.48 (VDD_2(P48)), VDD.TP
VDD: C23.1, IC8.8 (VDD), JP4.2, R10.2, R11.2, U$9.1 (3V3)
WL_D+: MOD1.D+, USB.7 (DP3)
WL_D-: MOD1.D-, USB.6 (DM3)

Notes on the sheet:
POWER SUPPLY
USB USER IO
RPI ZERO
POWER MONITOR
WIFI
LCD
USB HUB
AUDIO
raspberry pi zero portable computer
project A
jaromir.sukuba@gmail.com
RTC
22k/470p/DNP/10k(pot) alternatively

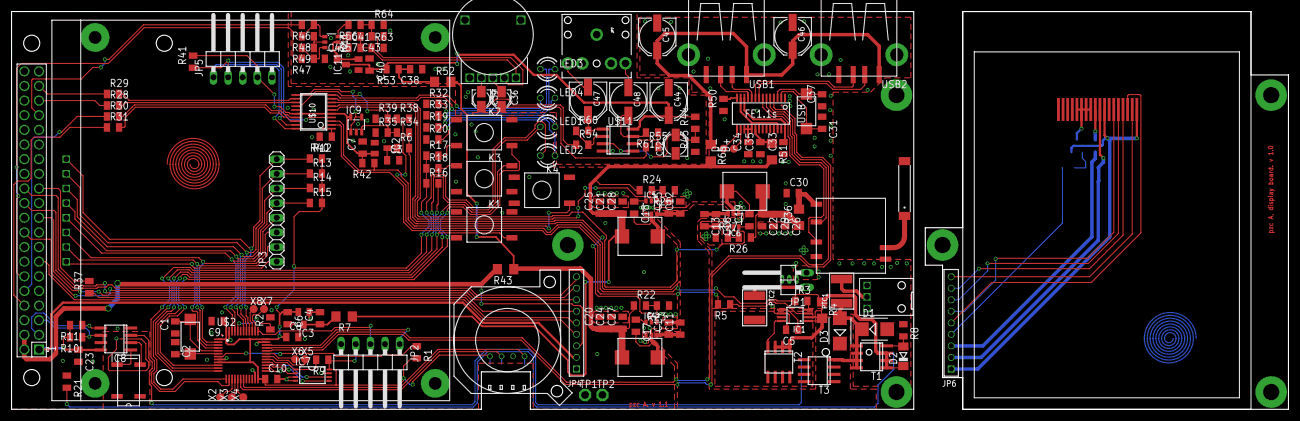
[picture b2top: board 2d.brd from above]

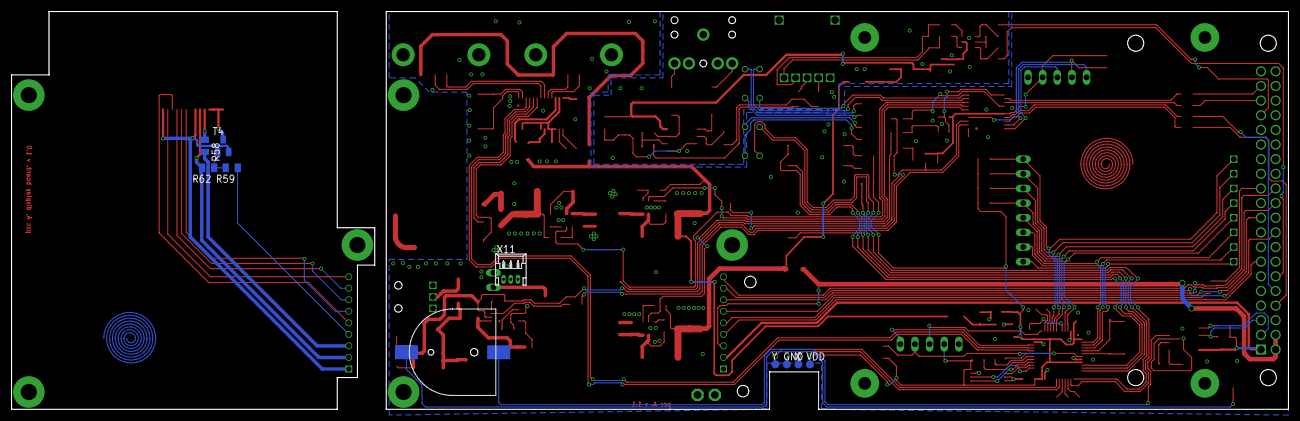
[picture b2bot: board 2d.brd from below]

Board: 2 copper layers, 221.5 x 69.0 mm, 185 parts (10 on the bottom side), 157 nets.

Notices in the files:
parts and their libraries:
SparkFun-Connectors: Licensing: CC v3.0 Share-Alike You are welcome to use this library for commercial purposes.
_microbuilder: This work is placed in the public domain, and may be freely used for commercial and non-commercial work with the following conditions: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
